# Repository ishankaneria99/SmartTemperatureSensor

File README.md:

# SmartTemperatureSensor
DHT22 sensor using an ESP32 microcontroller to send data towards a python script that utilizes a anthropic agent to run basic commands such as monitoring the temperature, and turning on a mini fan blade hooked up to a 130 DC motor. 

Referring to "image.jpeg" the wiring while "rudimentary" shows 2 LEDs that light based on a set temperature threshold. When the user prompts the agent to check the temperature, based on the temperature a fan is turned on automatically (RED led is turned on). There are also commands the user can give to enable or disable the fan regardless of temperature. 

7/27/26 -> Created physical layout and original code where agent talks through a python shell

7/28/26 -> Utilized streamlit to create a cleaner layout to send commands to the agent

7/30/26 -> Improved layout of streamlit app

8/2/26 -> Replaced Arduino with ESP32 and included KiCad Gerber file of the circuit on a PCB (did not include fan).

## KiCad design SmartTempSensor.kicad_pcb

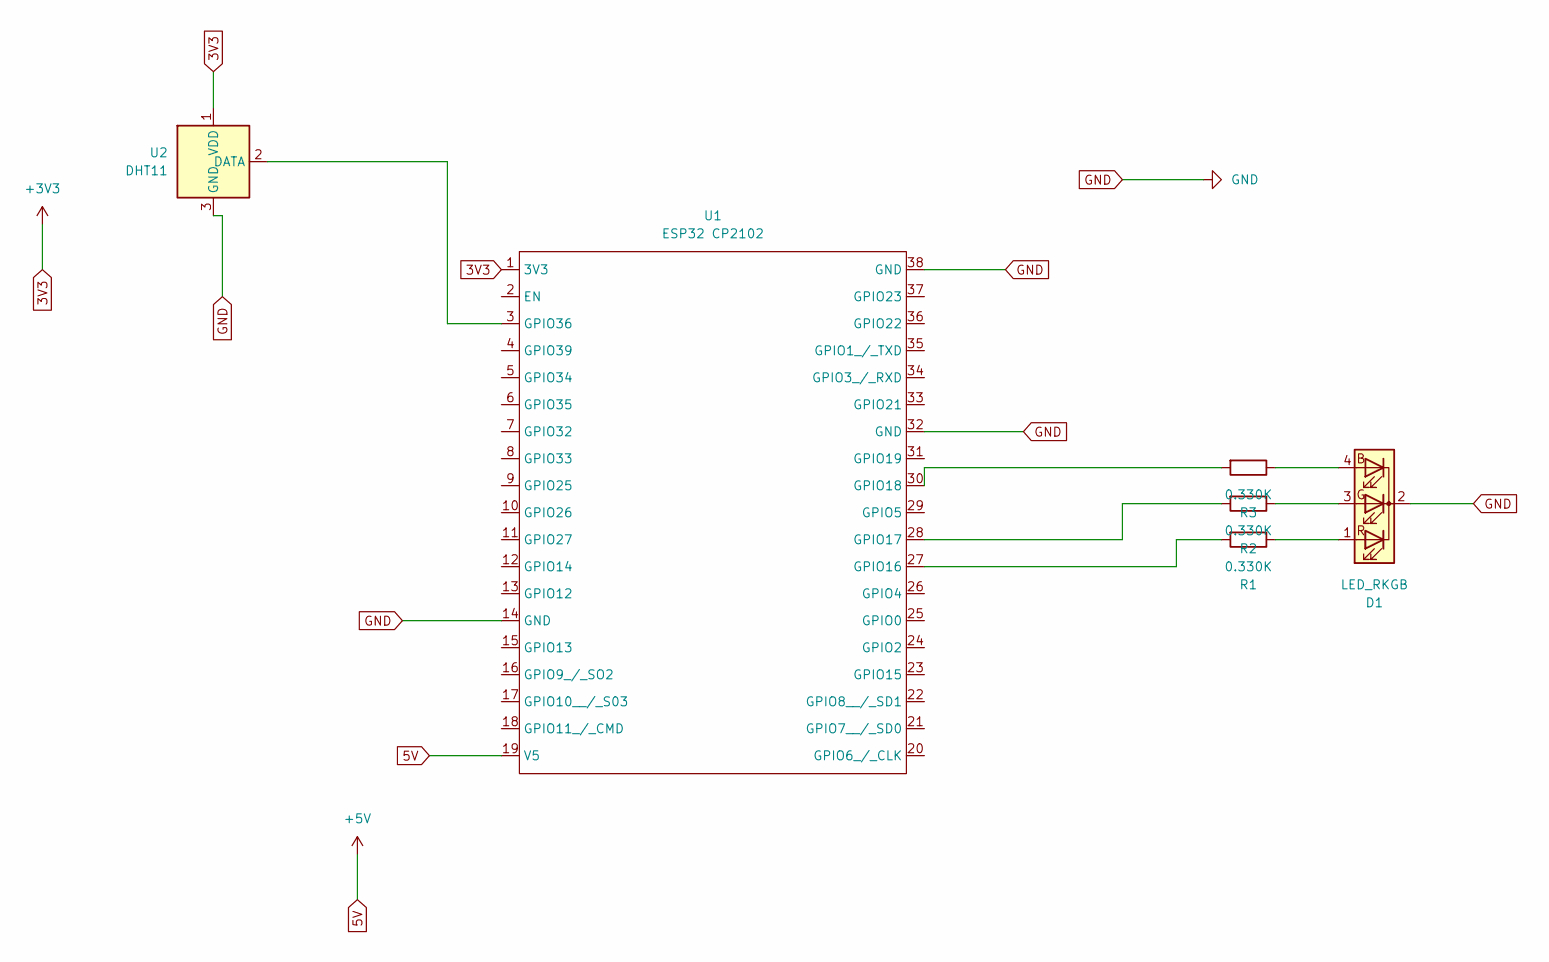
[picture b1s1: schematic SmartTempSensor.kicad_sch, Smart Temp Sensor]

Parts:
D1: LED_RKGB; LED_D5.0mm-4_RGB
R1, R2, R3: 0.330K; R_Axial_DIN0207_L6.3mm_D2.5mm_P7.62mm_Horizontal
U1: ESP32 CP2102; ESP32_38Pin (1)
U2: DHT11; Aosong_DHT11_5.5x12.0_P2.54mm

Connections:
3V3: U1.1 (3V3), U2.1 (VDD)
5V: U1.19 (V5)
GND: D1.2 (K), U1.14 (GND), U1.32 (GND), U1.38 (GND), U2.3 (GND)
unnamed: D1.4 (BA), R3.1
unnamed: D1.3 (GA), R2.1
unnamed: D1.1 (RA), R1.1
unnamed: R1.2, U1.27 (GPIO16)
unnamed: R2.2, U1.28 (GPIO17)
unnamed: R3.2, U1.30 (GPIO18)
unnamed: U1.3 (GPIO36), U2.2 (DATA)

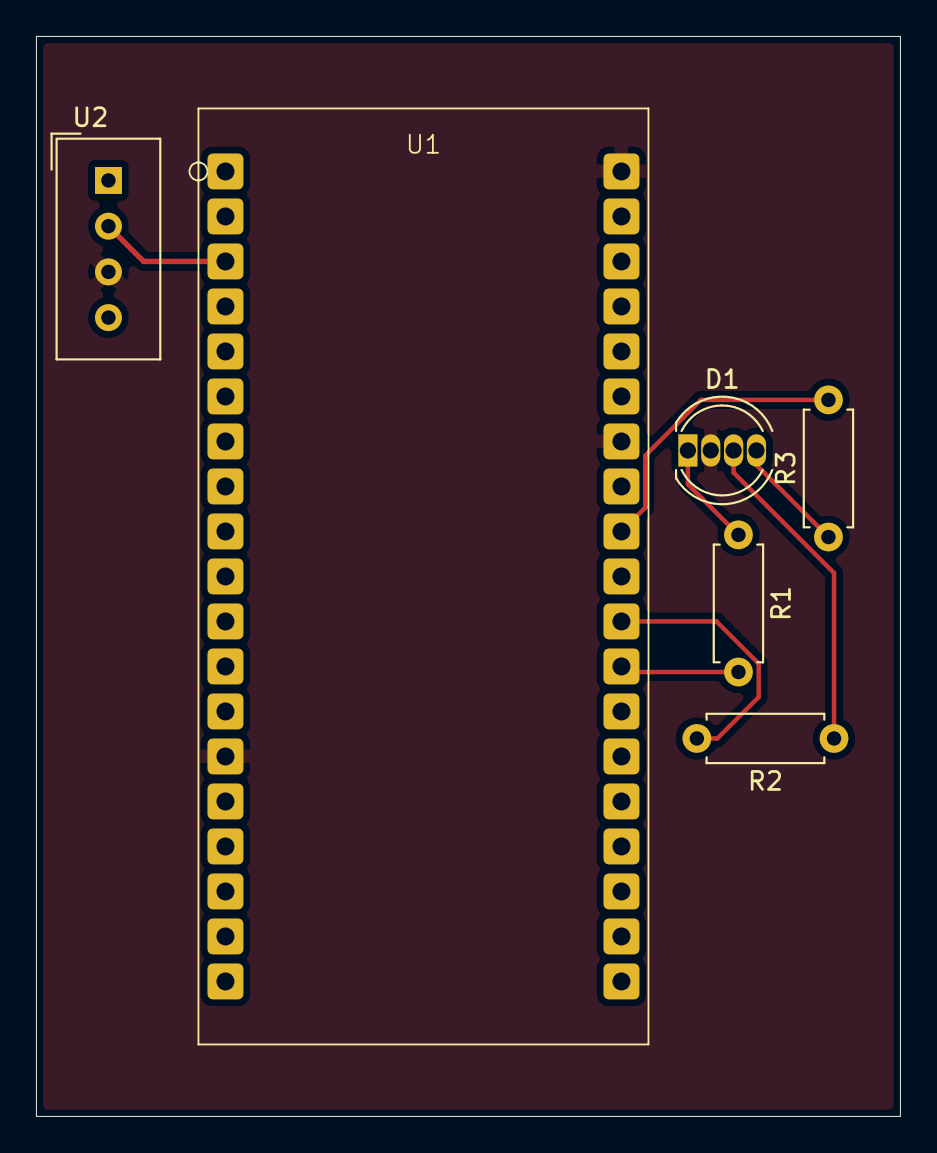
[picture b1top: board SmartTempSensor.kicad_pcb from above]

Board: 2 copper layers, 48.0 x 60.0 mm, 6 parts (0 on the bottom side), 9 nets.
